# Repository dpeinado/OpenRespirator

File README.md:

# OpenRespirator
Software & Hardware for Open Respirator Project <br>

HW and system dodumentation are in the Doc directory <br>

## Contributors
- The system design is done by: Frede Jensen <br>
- Project coordination: Enrique Ramirez and Ramon Ruiz (Ennomotive) <br>
- Hardware & Software: David Ortiz, Rubén Perez de Aranda and Carlos Pardo <br>
- Collaborators: 
- - Intersurgical: Sara Rodriguez, Bill Barners, Mike Hinton <br>
- - Vithas Sanidad : Ignacio Narvaez <br>
- - McFly: Enrique, Marino y Daniel
  
## Sponsors: <br>

## ToDo list
### System

### Assembly

### Production
- Prepare production documentation
- - Define part alternatives
- Define production test & calibration
### Electronics
- Documentation
- - Electronics production test
### Firmware
- Monitor:
- Controller:
### Test & Validation
- Clinic test:
### Certification
- Documentation
- Presented to gobernment

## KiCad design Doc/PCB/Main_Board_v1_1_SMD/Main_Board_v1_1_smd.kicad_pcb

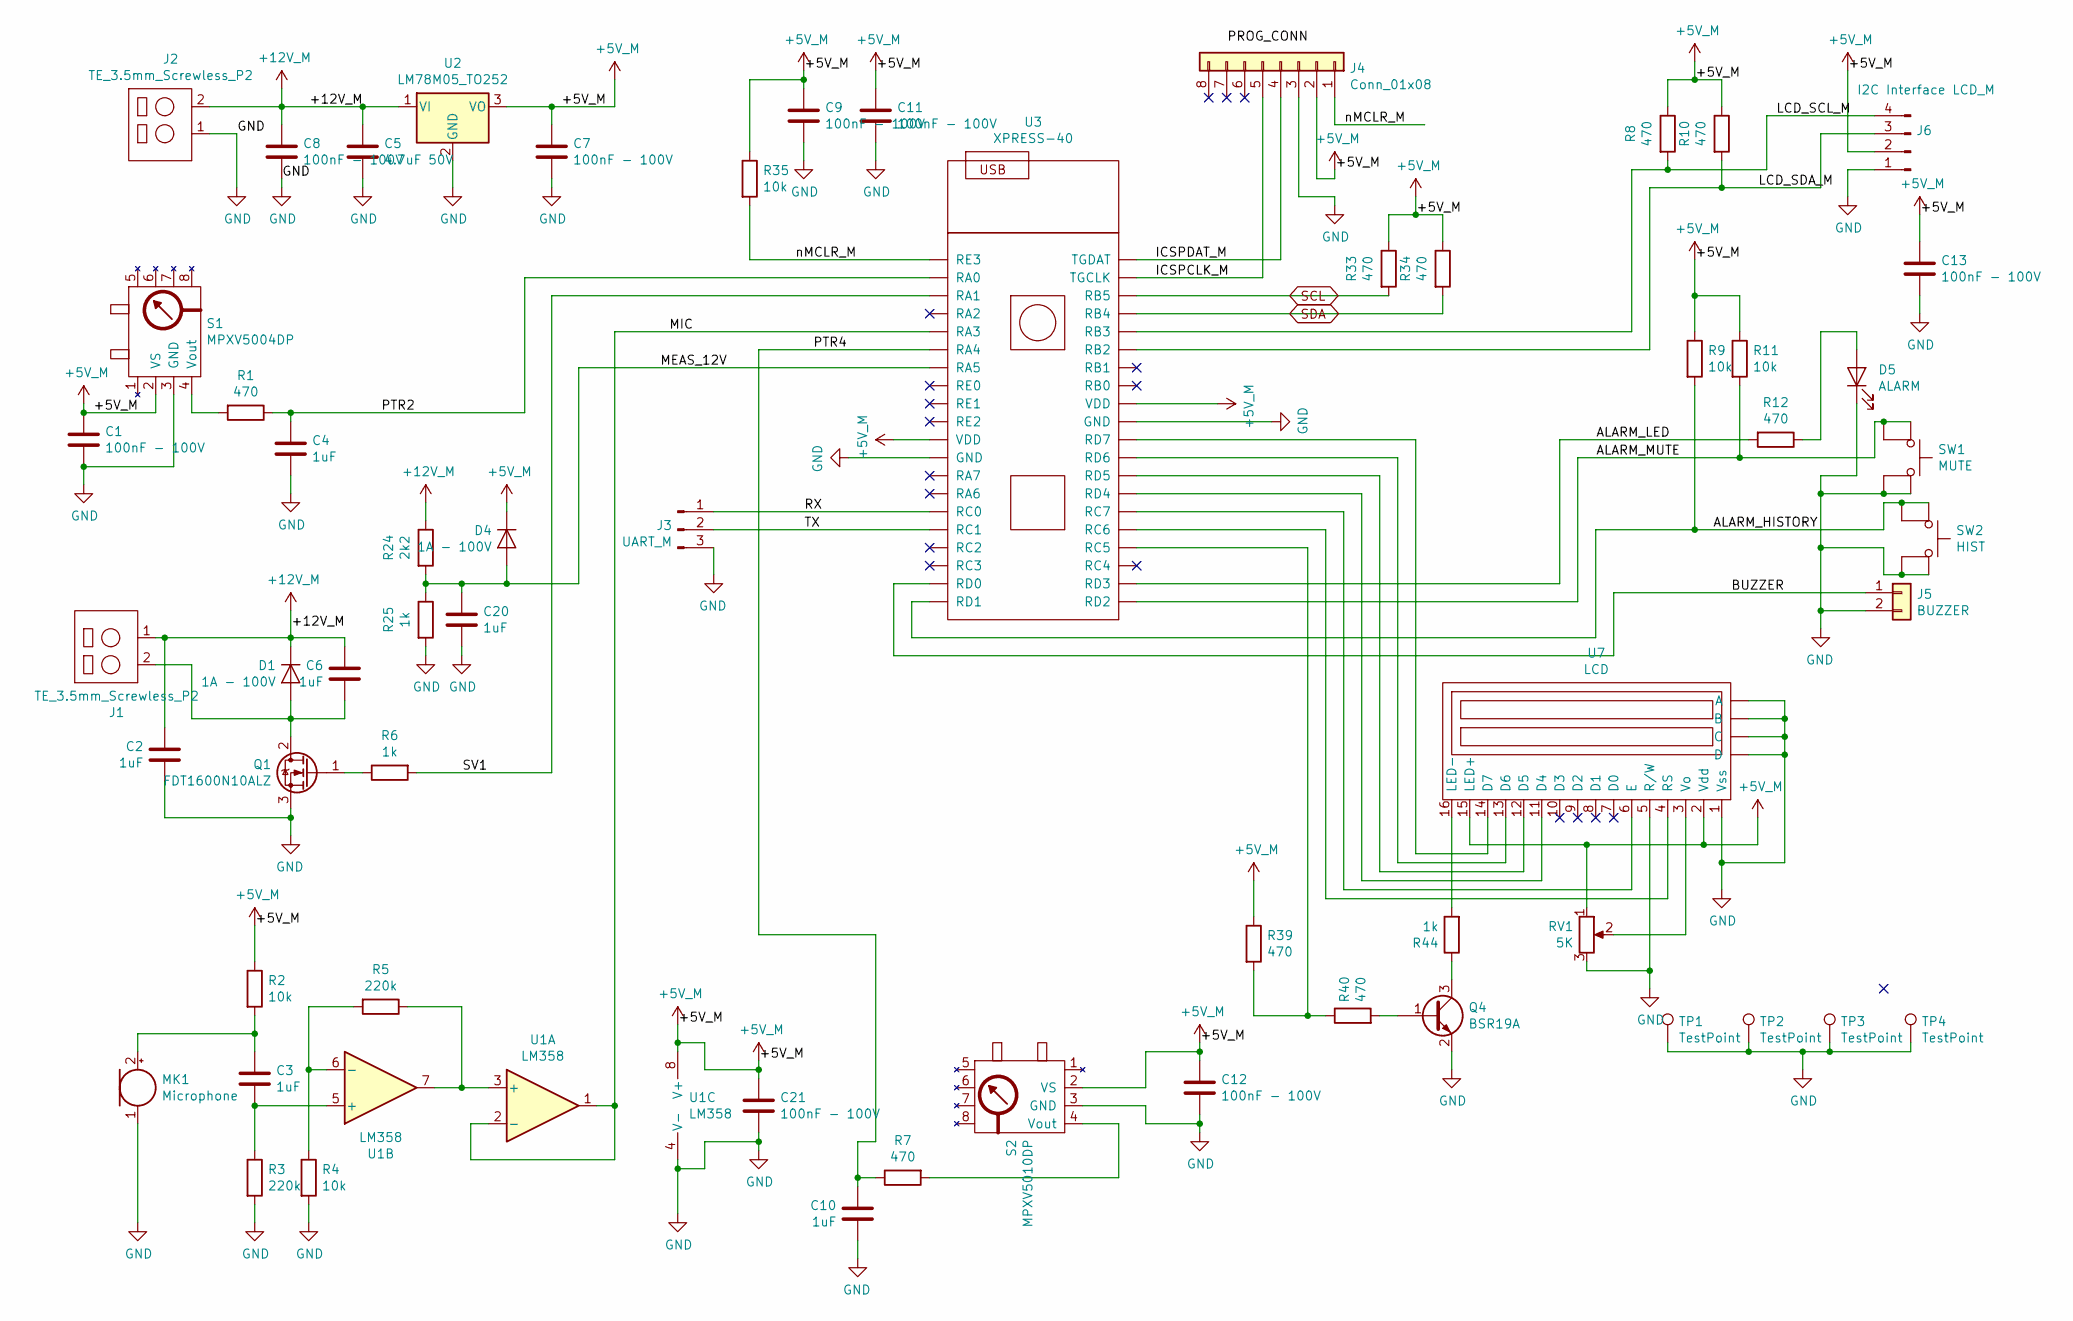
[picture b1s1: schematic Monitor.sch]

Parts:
C1, C7, C8, C9, C11, C12, C13, C21: 100nF - 100V; C_1206_3216Metric_Pad1.42x1.75mm_HandSolder
C2, C3, C4, C6, C10, C20: 1uF; C_1206_3216Metric_Pad1.42x1.75mm_HandSolder
C5: 4.7uF 50V; CP_Radial_D5.0mm_P2.00mm
D1, D4: 1A - 100V; D_SMA-SMB_Universal_Handsoldering
D5: ALARM; LED_D3.0mm
J1, J2: TE_3.5mm_Screwless_P2; PinHeader_1x02_Screwless_3.5mm
J3: UART_M; PinHeader_1x03_P2.54mm_Vertical
J4: Conn_01x08; PinHeader_1x08_P2.54mm_Horizontal
J5: BUZZER; PH_2_pol
J6: I2C Interface LCD_M; PH_4_pol
MK1: Microphone; MIC
Q1: FDT1600N10ALZ; SOT-223-3_TabPin2
Q4: BSR19A; TSOT-23
R1, R7, R8, R10, R12, R33, R34, R39, R40: 470; R_0603_1608Metric_Pad1.05x0.95mm_HandSolder
R2, R4, R9, R11, R35: 10k; R_0603_1608Metric_Pad1.05x0.95mm_HandSolder
R3, R5: 220k; R_0603_1608Metric_Pad1.05x0.95mm_HandSolder
R6, R25, R44: 1k; R_0603_1608Metric_Pad1.05x0.95mm_HandSolder
R24: 2k2; R_0603_1608Metric_Pad1.05x0.95mm_HandSolder
RV1: 5K; Potentiometer_Vishay_TS53YJ_Vertical
S1: MPXV5004DP; 1351-01
S2: MPXV5010DP; 1351-01
SW1: MUTE; SW_PUSH_6mm_H13mm
SW2: HIST; SW_PUSH_6mm_H13mm
TP1, TP2, TP3, TP4: TestPoint; LCD_DRILL
U1: LM358; SOIC-8-1EP_3.9x4.9mm_P1.27mm_EP2.41x3.3mm
U2: LM78M05_TO252; TO-252-2
U3: XPRESS-40; UQFN-40-1EP_5x5mm_P0.4mm_EP3.8x3.8mm
U7: LCD; LCD_2x16

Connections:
+5V_M: C1.1, C7.1, C9.1, C11.1, C12.1, C13.1, C21.1, D4.1 (K), J4.2, J6.2, R2.1, R8.1, R9.1, R10.1, R11.1, R33.1, R34.1, R35.1, R39.1, RV1.1, S1.2 (VS), S2.2 (VS), U1.8 (V+), U2.3 (VO), U3.11 (VDD), U3.32 (VDD), U7.2 (Vdd), U7.15 (LED+)
+12V_M: C2.1, C5.1, C6.1, C8.1, D1.1 (K), J1.1, J2.2, R24.1, U2.1 (VI)
/Monitor/ALARM_HISTORY: R9.2, SW2.1, U3.20 (RD1)
/Monitor/ALARM_LED: R12.2, U3.22 (RD3)
/Monitor/ALARM_MUTE: R11.2, SW1.1, U3.21 (RD2)
/Monitor/BUZZER: J5.1, U3.19 (RD0)
/Monitor/ICSPCLK_M: J4.5, U3.39 (TGCLK)
/Monitor/ICSPDAT_M: J4.4, U3.40 (TGDAT)
/Monitor/LCD_SCL_M: J6.4, R8.2, U3.36 (RB3)
/Monitor/LCD_SDA_M: J6.3, R10.2, U3.35 (RB2)
/Monitor/MEAS_12V: C20.1, D4.2 (A), R24.2, R25.1, U3.7 (RA5)
/Monitor/MIC: U1.1, U1.2 (-), U3.5 (RA3)
/Monitor/PTR2: C4.1, R1.1, U3.2 (RA0)
/Monitor/PTR4: C10.1, R7.1, U3.6 (RA4)
/Monitor/RX: J3.1, U3.15 (RC0)
/Monitor/SV1: R6.2, U3.3 (RA1)
/Monitor/TX: J3.2, U3.16 (RC1)
/Monitor/nMCLR_M: J4.1, R35.2, U3.1 (RE3)
GND: C1.2, C2.2, C4.2, C5.2, C7.2, C8.2, C9.2, C10.2, C11.2, C12.2, C13.2, C20.2, C21.2, D5.1 (K), J2.1, J3.3, J4.3, J5.2, J6.1, MK1.1 (-), Q1.3 (S), Q4.2 (E), R3.2, R4.2, R25.2, RV1.3, S1.3 (GND), S2.3 (GND), SW1.2, SW2.2, TP1.1, TP2.1, TP3.1, TP4.1, U1.4 (V-), U2.2 (GND), U3.12 (GND), U3.31 (GND), U7.1 (Vss), U7.5 (R/W), U7.~ (A); also elsewhere on the board
unnamed: C3.1, MK1.2 (+), R2.2
unnamed: C3.2, R3.1, U1.5 (+)
unnamed: C6.2, D1.2 (A), J1.2, Q1.2 (D)
unnamed: D5.2 (A), R12.1
unnamed: Q1.1 (G), R6.1
unnamed: Q4.1 (B), R40.2
unnamed: Q4.3 (C), R44.1
unnamed: R1.2, S1.4 (Vout)
unnamed: R4.1, R5.2, U1.6 (-)
unnamed: R5.1, U1.3 (+), U1.7
unnamed: R7.2, S2.4 (Vout)
unnamed: R39.2, R40.1, U3.24 (RC5)
unnamed: R44.2, U7.16 (LED-)
unnamed: RV1.2, U7.3 (Vo)
unnamed: U3.25 (RC6), U7.4 (RS)
unnamed: U3.26 (RC7), U7.6 (E)
unnamed: U3.27 (RD4), U7.11 (D4)
unnamed: U3.28 (RD5), U7.12 (D5)
unnamed: U3.29 (RD6), U7.13 (D6)
unnamed: U3.30 (RD7), U7.14 (D7)
SCL: R33.2, U3.38 (RB5); also elsewhere on the board
SDA: R34.2, U3.37 (RB4); also elsewhere on the board

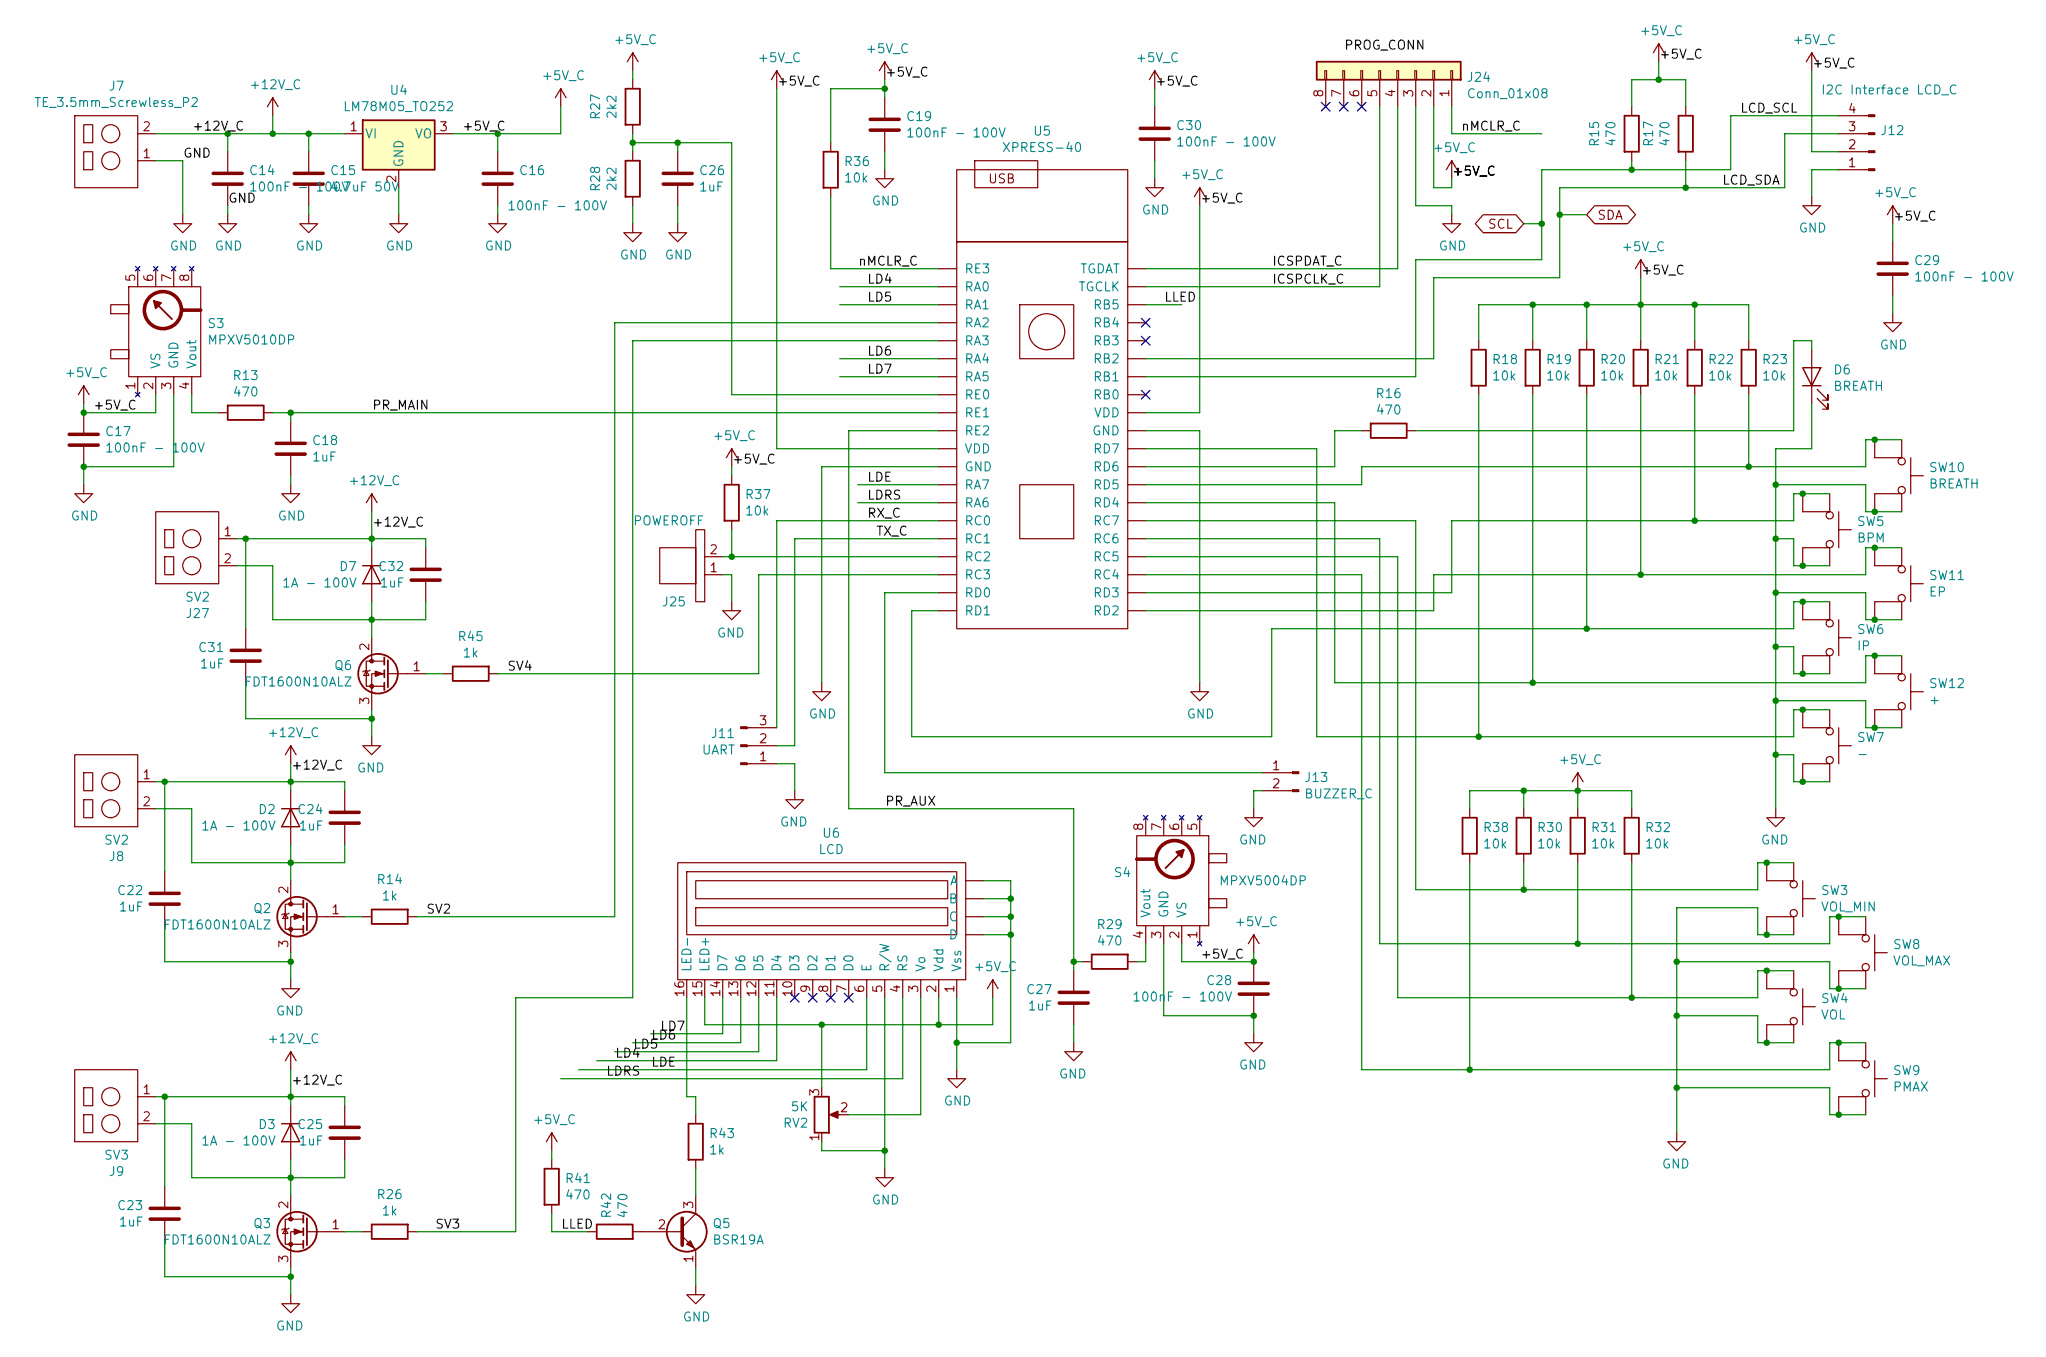
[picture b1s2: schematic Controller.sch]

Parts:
C14, C16, C17, C19, C28, C29, C30: 100nF - 100V; C_1206_3216Metric_Pad1.42x1.75mm_HandSolder
C15: 4.7uF 50V; CP_Radial_D5.0mm_P2.00mm
C18, C22, C23, C24, C25, C26, C27, C31, C32: 1uF; C_1206_3216Metric_Pad1.42x1.75mm_HandSolder
D2, D3, D7: 1A - 100V; D_SMA-SMB_Universal_Handsoldering
D6: BREATH; LED_D3.0mm
J7: TE_3.5mm_Screwless_P2; PinHeader_1x02_Screwless_3.5mm
J8, J27: SV2; PinHeader_1x02_Screwless_3.5mm
J9: SV3; PinHeader_1x02_Screwless_3.5mm
J11: UART; PinHeader_1x03_P2.54mm_Vertical
J12: I2C Interface LCD_C; PH_4_pol
J13: BUZZER_C; PinHeader_1x02_P2.54mm_Vertical
J24: Conn_01x08; PinHeader_1x08_P2.54mm_Horizontal
J25: POWEROFF; PH_2_pol
Q2, Q3, Q6: FDT1600N10ALZ; SOT-223-3_TabPin2
Q5: BSR19A; TSOT-23
R13, R15, R16, R17, R29, R41, R42: 470; R_0603_1608Metric_Pad1.05x0.95mm_HandSolder
R14, R26, R43, R45: 1k; R_0603_1608Metric_Pad1.05x0.95mm_HandSolder
R18, R19, R20, R21, R22, R23, R30, R31, R32, R36, R37, R38: 10k; R_0603_1608Metric_Pad1.05x0.95mm_HandSolder
R27, R28: 2k2; R_0603_1608Metric_Pad1.05x0.95mm_HandSolder
RV2: 5K; Potentiometer_Vishay_TS53YJ_Vertical
S3: MPXV5010DP; 1351-01
S4: MPXV5004DP; 1351-01
SW3: VOL_MIN; SW_PUSH_6mm_H13mm
SW4: VOL; SW_PUSH_6mm_H13mm
SW5: BPM; SW_PUSH_6mm_H13mm
SW6: IP; SW_PUSH_6mm_H13mm
SW7: -; SW_PUSH_6mm_H13mm
SW8: VOL_MAX; SW_PUSH_6mm_H13mm
SW9: PMAX; SW_PUSH_6mm_H13mm
SW10: BREATH; SW_PUSH_6mm_H13mm
SW11: EP; SW_PUSH_6mm_H13mm
SW12: +; SW_PUSH_6mm_H13mm
U4: LM78M05_TO252; TO-252-2
U5: XPRESS-40; UQFN-40-1EP_5x5mm_P0.4mm_EP3.8x3.8mm
U6: LCD; LCD_2x16

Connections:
+5V_C: C16.1, C17.1, C19.1, C28.1, C29.1, C30.1, J12.2, J24.2, R15.1, R17.1, R18.1, R19.1, R20.1, R21.1, R22.1, R23.1, R27.1, R30.1, R31.1, R32.1, R36.1, R37.1, R38.1, R41.1, RV2.3, S3.2 (VS), S4.2 (VS), U4.3 (VO), U5.11 (VDD), U5.32 (VDD), U6.2 (Vdd), U6.15 (LED+)
+12V_C: C14.1, C15.1, C22.1, C23.1, C24.1, C25.1, C31.1, C32.1, D2.1 (K), D3.1 (K), D7.1 (K), J7.2, J8.1, J9.1, J27.1, U4.1 (VI)
/Controller/ICSPCLK_C: J24.5, U5.39 (TGCLK)
/Controller/ICSPDAT_C: J24.4, U5.40 (TGDAT)
/Controller/LD4: U5.2 (RA0), U6.11 (D4)
/Controller/LD5: U5.3 (RA1), U6.12 (D5)
/Controller/LD6: U5.6 (RA4), U6.13 (D6)
/Controller/LD7: U5.7 (RA5), U6.14 (D7)
/Controller/LDE: U5.13 (RA7), U6.6 (E)
/Controller/LDRS: U5.14 (RA6), U6.4 (RS)
/Controller/LLED: R41.2, R42.1, U5.38 (RB5)
/Controller/PR_AUX: C27.1, R29.1, U5.10 (RE2)
/Controller/PR_MAIN: C18.1, R13.1, U5.9 (RE1)
/Controller/RX_C: J11.3, U5.15 (RC0)
/Controller/SV2: R14.2, U5.4 (RA2)
/Controller/SV3: R26.2, U5.5 (RA3)
/Controller/SV4: R45.2, U5.18 (RC3)
/Controller/TX_C: J11.2, U5.16 (RC1)
/Controller/nMCLR_C: J24.1, R36.2, U5.1 (RE3)
GND: C14.2, C15.2, C16.2, C17.2, C18.2, C19.2, C22.2, C23.2, C26.2, C27.2, C28.2, C29.2, C30.2, C31.2, D6.1 (K), J7.1, J11.1, J12.1, J13.2, J24.3, J25.1, Q2.3 (S), Q3.3 (S), Q5.1 (E), Q6.3 (S), R28.2, RV2.1, S3.3 (GND), S4.3 (GND), SW3.2, SW4.2, SW5.2, SW6.2, SW7.2, SW8.2, SW9.2, SW10.2, SW11.2, SW12.2, U4.2 (GND), U5.12 (GND), U5.31 (GND), U6.1 (Vss), U6.5 (R/W), U6.~ (A); also elsewhere on the board
unnamed: C24.2, D2.2 (A), J8.2, Q2.2 (D)
unnamed: C25.2, D3.2 (A), J9.2, Q3.2 (D)
unnamed: C26.1, R27.2, R28.1, U5.8 (RE0)
unnamed: C32.2, D7.2 (A), J27.2, Q6.2 (D)
unnamed: D6.2 (A), R16.1
unnamed: J13.1, U5.19 (RD0)
unnamed: J25.2, R37.2, U5.17 (RC2)
unnamed: Q2.1 (G), R14.1
unnamed: Q3.1 (G), R26.1
unnamed: Q5.2 (B), R42.2
unnamed: Q5.3 (C), R43.2
unnamed: Q6.1 (G), R45.1
unnamed: R13.2, S3.4 (Vout)
unnamed: R16.2, U5.29 (RD6)
unnamed: R18.2, SW7.1, U5.30 (RD7)
unnamed: R19.2, SW12.1, U5.27 (RD4)
unnamed: R20.2, SW6.1, U5.20 (RD1)
unnamed: R21.2, SW11.1, U5.21 (RD2)
unnamed: R22.2, SW5.1, U5.22 (RD3)
unnamed: R23.2, SW10.1, U5.28 (RD5)
unnamed: R29.2, S4.4 (Vout)
unnamed: R30.2, SW3.1, U5.26 (RC7)
unnamed: R31.2, SW8.1, U5.25 (RC6)
unnamed: R32.2, SW4.1, U5.24 (RC5)
unnamed: R38.2, SW9.1, U5.23 (RC4)
unnamed: R43.1, U6.16 (LED-)
unnamed: RV2.2, U6.3 (Vo)
SCL: J12.4, R15.2, U5.34 (RB1); also elsewhere on the board
SDA: J12.3, R17.2, U5.35 (RB2); also elsewhere on the board

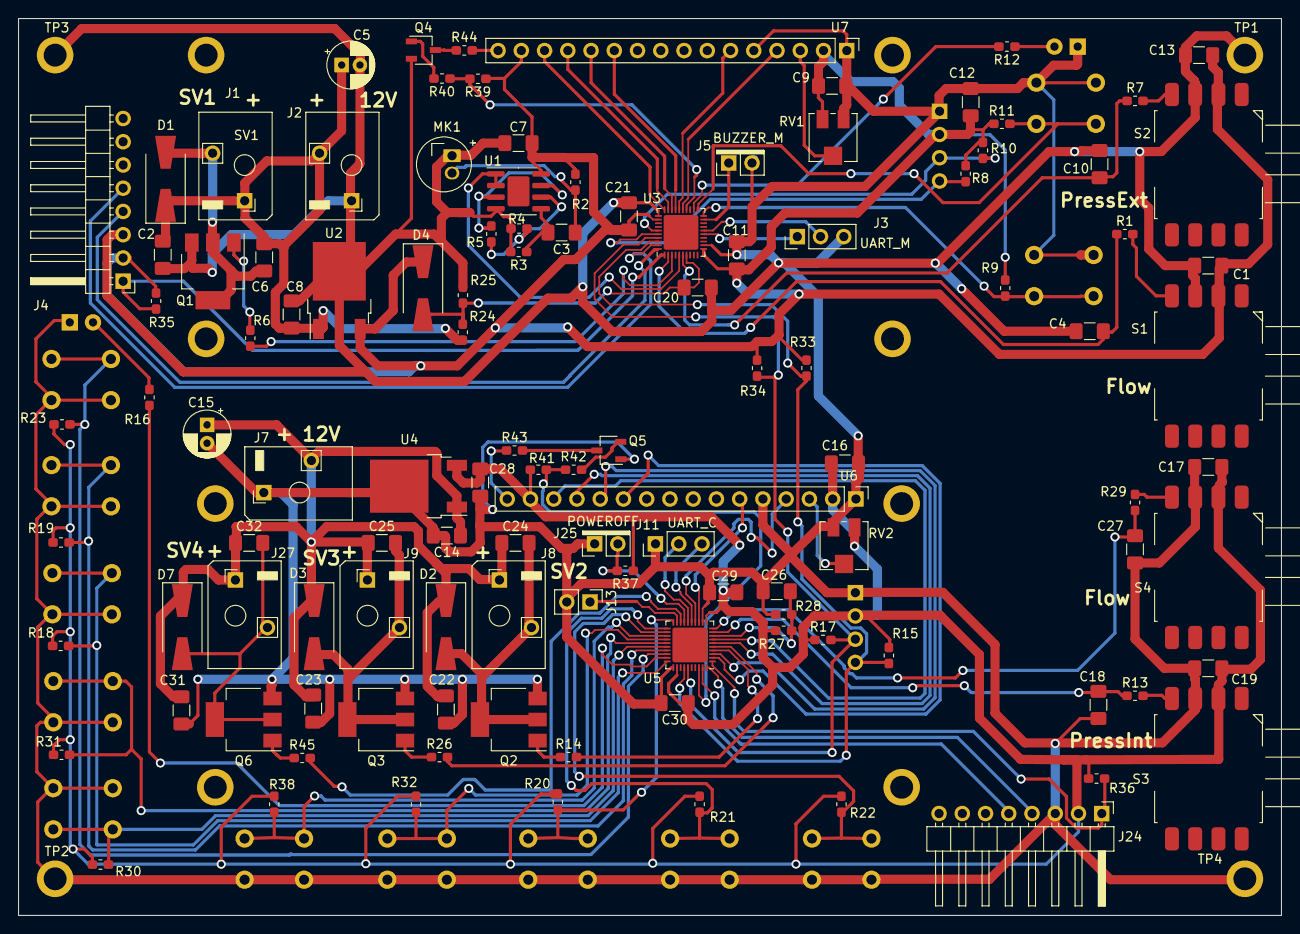
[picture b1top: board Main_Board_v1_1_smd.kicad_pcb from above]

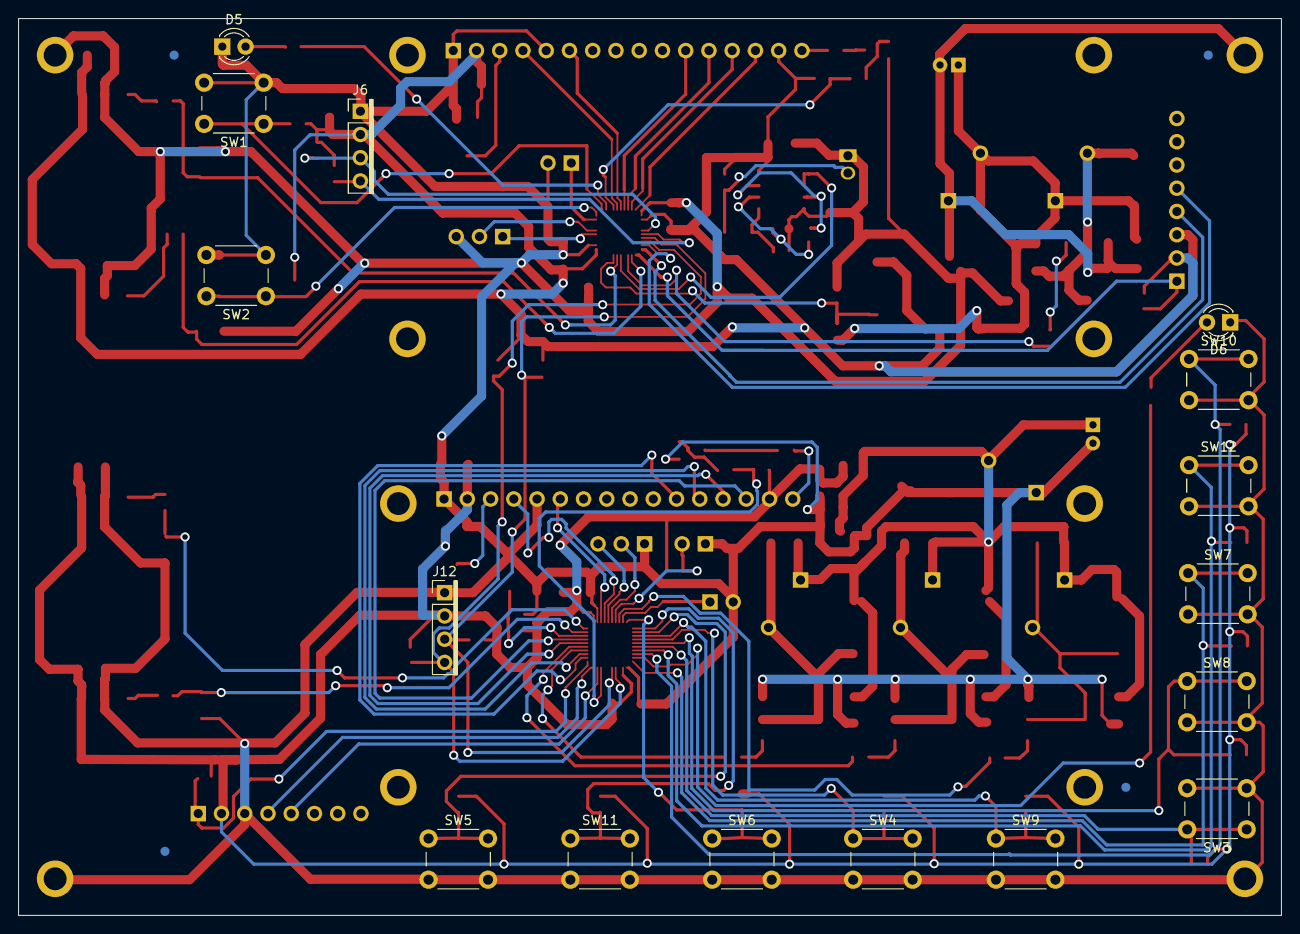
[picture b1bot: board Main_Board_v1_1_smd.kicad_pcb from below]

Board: 2 copper layers, 138.0 x 98.0 mm, 139 parts (16 on the bottom side), 87 nets.

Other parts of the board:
FIDUCIAL_TEST_PCB_1C, FIDUCIAL_TEST_PCB_1C#2, FIDUCIAL_TEST_PCB_1C#3, FIDUCIAL_TEST_PCB_1C#4: VAL**; FIDUCIAL_TEST_PCB_1C

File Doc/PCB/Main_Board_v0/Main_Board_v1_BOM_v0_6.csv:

Reference, Quantity, Value, Footprint, Datasheet
C10 C2 C6 C3 C4 C20 C22 C24 C23 C25 C18 C27 C26 ,13,"1uF","Capacitor_THT:C_Rect_L13.0mm_W4.0mm_P10.00mm_FKS3_FKP3_MKS4","https://es.rs-online.com/web/p/condensadores-de-pelicula-de-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"
C12 C13 C11 C8 C9 C1 C7 C21 C19 C14 C16 C29 C17 C28 C30 ,15,"100nF - 100V","Capacitor_THT:C_Rect_L7.2mm_W2.5mm_P5.00mm_FKS2_FKP2_MKS2_MKP2","https://es.rs-online.com/web/p/condensadores-de-pelicula-de-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"
C5 C15 ,2,"4.7uF 50V","Capacitor_THT:CP_Radial_D5.0mm_P2.00mm","https://es.rs-online.com/web/p/condensadores-de-aluminio/1701286/"
D1 D4 D2 D3 ,4,"1N4007","Diode_THT:D_DO-41_SOD81_P10.16mm_Horizontal","https://es.rs-online.com/web/p/diodos-schottky-y-rectificado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"
J10 ,1,"BPM","Ventilator:PushButton","https://es.rs-online.com/web/p/botones-pulsadores/7346827/"
J11 ,1,"UART","Connector_PinHeader_2.54mm:PinHeader_1x03_P2.54mm_Vertical","~"
J12 ,1,"I2C Interface LCD_C","Ventilator:PH_4_pol","~"
J13 ,1,"BUZZER_C","Connector_PinHeader_2.54mm:PinHeader_1x02_P2.54mm_Vertical","https://es.rs-online.com/web/p/componentes-de-piezo-buzzer/6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"
J14 ,1,"MUTE","Ventilator:PushButton_LED","https://es.rs-online.com/web/p/botones-pulsadores/8207521/"
J15 ,1,"HISTORY","Ventilator:PushButton","https://es.rs-online.com/web/p/botones-pulsadores/7346827/"
J16 ,1,"IP","Ventilator:PushButton","https://es.rs-online.com/web/p/botones-pulsadores/7346827/"
J17 ,1,"-","Ventilator:PushButton","https://es.rs-online.com/web/p/botones-pulsadores/7346827/"
J18 ,1,"BREATH","Ventilator:PushButton_LED","https://es.rs-online.com/web/p/botones-pulsadores/8207533/"
J19 ,1,"EP","Ventilator:PushButton","https://es.rs-online.com/web/p/botones-pulsadores/7346827/"
J2 J1 J7 ,3,"TE_3.5mm_Screwless_P2","Ventilator:PinHeader_1x02_Screwless_3.5mm","https://es.rs-online.com/web/p/bloques-terminales-para-pcb/1232052/"
J20 ,1,"+","Ventilator:PushButton","https://es.rs-online.com/web/p/botones-pulsadores/7346827/"
J21 ,1,"VOL_MIN","Ventilator:PushButton","https://es.rs-online.com/web/p/botones-pulsadores/7346827/"
J22 ,1,"VOL","Ventilator:PushButton","https://es.rs-online.com/web/p/botones-pulsadores/7346827/"
J23 ,1,"VOL_MAX","Ventilator:PushButton","https://es.rs-online.com/web/p/botones-pulsadores/7346827/"
J3 ,1,"UART_M","Connector_PinHeader_2.54mm:PinHeader_1x03_P2.54mm_Vertical","~"
J4 J24 ,2,"Conn_01x08","Connector_PinHeader_2.54mm:PinHeader_1x08_P2.54mm_Horizontal","~"
J5 ,1,"BUZZER","Ventilator:PH_2_pol","https://es.rs-online.com/web/p/componentes-de-piezo-buzzer/6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"
J6 ,1,"I2C Interface LCD_M","Ventilator:PH_4_pol","~"
J8 ,1,"SV2","Ventilator:PinHeader_1x02_Screwless_3.5mm","https://es.rs-online.com/web/p/bloques-terminales-para-pcb/1232052/"
J9 ,1,"SV3","Ventilator:PinHeader_1x02_Screwless_3.5mm","https://es.rs-online.com/web/p/bloques-terminales-para-pcb/1232052/"
MK1 ,1,"Microphone","Ventilator:MIC","https://es.rs-online.com/web/p/componentes-de-microfono-para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"
Q1 Q2 Q3 ,3,"STP24NF10 ","Package_TO_SOT_THT:TO-220-3_Vertical","https://es.rs-online.com/web/p/mosfet/6875377/"
R24 ,1,"22k","Resistor_THT:R_Axial_DIN0207_L6.3mm_D2.5mm_P10.16mm_Horizontal","~"
R3 R5 ,2,"220k","Resistor_THT:R_Axial_DIN0207_L6.3mm_D2.5mm_P10.16mm_Horizontal","~"
R4 R2 R11 R9 R25 R35 R19 R20 R21 R22 R23 R18 R27 R28 R31 R32 R30 R36 ,18,"10k","Resistor_THT:R_Axial_DIN0207_L6.3mm_D2.5mm_P10.16mm_Horizontal","~"
R6 R14 R26 ,3,"50","Resistor_THT:R_Axial_DIN0207_L6.3mm_D2.5mm_P10.16mm_Horizontal","~"
R7 R10 R8 R12 R1 R34 R33 R16 R17 R15 R13 R29 ,12,"470","Resistor_THT:R_Axial_DIN0207_L6.3mm_D2.5mm_P10.16mm_Horizontal","~"
S1 S2 S3 S4 ,4,"MPXV5004DP","Ventilator:1351-01","https://es.rs-online.com/web/p/sensores-de-presion/9227399/"
TP3 TP2 TP1 TP4 TP7 TP6 TP5 TP8 TP12 TP11 TP10 TP13 ,12,"TestPoint","Ventilator:LCD_DRILL","~"
TP9 ,1,"TestPoint_Alt","Ventilator:pcb","~"
U1 ,1,"LM358","Package_DIP:DIP-8_W7.62mm_LongPads","http://www.ti.com/lit/ds/symlink/lm2904-n.pdf"
U2 U4 ,2,"LM7805_TO220","Package_TO_SOT_THT:TO-220-3_Vertical","http://www.fairchildsemi.com/ds/LM/LM7805.pdf"
U3 U5 ,2,"XPRESS-40","Ventilator:EXPRESS-40_DIP_40","https://es.rs-online.com/web/p/kits-de-desarrollo-de-procesa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"

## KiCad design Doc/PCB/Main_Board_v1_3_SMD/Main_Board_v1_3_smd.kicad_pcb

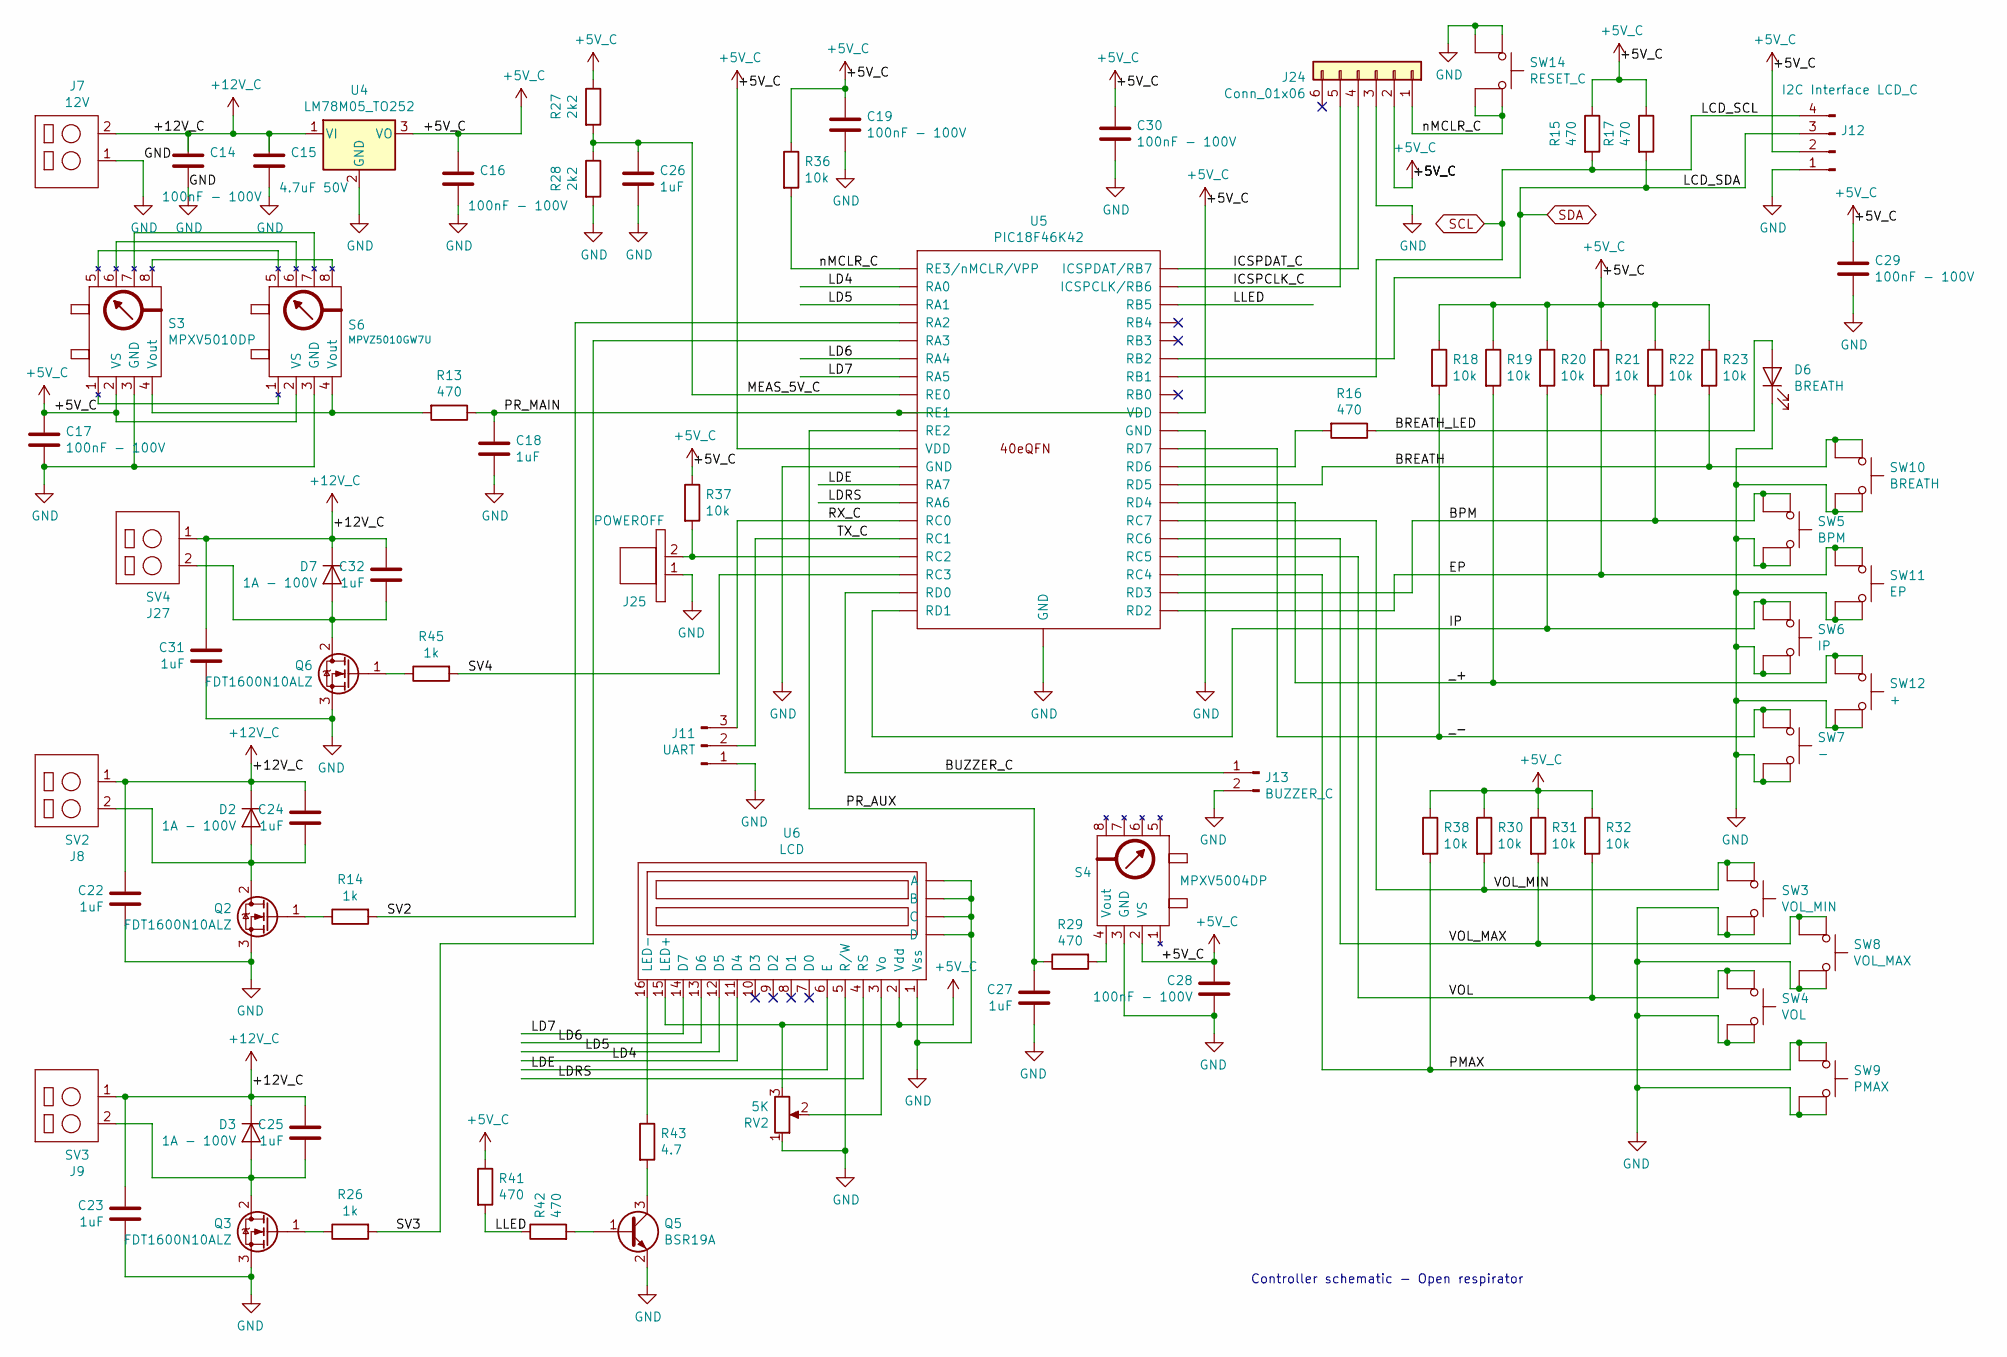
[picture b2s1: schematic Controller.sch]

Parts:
C14, C16, C17, C19, C28, C29, C30: 100nF - 100V; C_1206_3216Metric_Pad1.42x1.75mm_HandSolder
C15: 4.7uF 50V; CP_Radial_D5.0mm_P2.00mm
C18, C22, C23, C24, C25, C26, C27, C31, C32: 1uF; C_1206_3216Metric_Pad1.42x1.75mm_HandSolder
D2, D3, D7: 1A - 100V; D_SMA-SMB_Universal_Handsoldering
D6: BREATH; LED_D3.0mm
J7: 12V; PinHeader_1x02_Screwless_3.5mm
J8: SV2; PinHeader_1x02_Screwless_3.5mm
J9: SV3; PinHeader_1x02_Screwless_3.5mm
J11: UART; PinHeader_1x03_P2.54mm_Vertical
J12: I2C Interface LCD_C; PH_4_pol
J13: BUZZER_C; PinHeader_1x02_P2.54mm_Vertical
J24: Conn_01x06; PinHeader_1x06_P2.54mm_Horizontal
J25: POWEROFF; PH_2_pol
J27: SV4; PinHeader_1x02_Screwless_3.5mm
Q2, Q3, Q6: FDT1600N10ALZ; SOT-223-3_TabPin2
Q5: BSR19A; SOT-23
R13, R15, R16, R17, R29, R41, R42: 470; R_0603_1608Metric_Pad1.05x0.95mm_HandSolder
R14, R26, R45: 1k; R_0603_1608Metric_Pad1.05x0.95mm_HandSolder
R18, R19, R20, R21, R22, R23, R30, R31, R32, R36, R37, R38: 10k; R_0603_1608Metric_Pad1.05x0.95mm_HandSolder
R27, R28: 2k2; R_0603_1608Metric_Pad1.05x0.95mm_HandSolder
R43: 4.7; R_0603_1608Metric_Pad1.05x0.95mm_HandSolder
RV2: 5K; Potentiometer_Vishay_TS53YJ_Vertical
S3: MPXV5010DP; 1351-01
S4: MPXV5004DP; 1351-01
S6: MPVZ5010GW7U; 1560-03
SW3: VOL_MIN; SW_PUSH_6mm_H13mm
SW4: VOL; SW_PUSH_6mm_H13mm
SW5: BPM; SW_PUSH_6mm_H13mm
SW6: IP; SW_PUSH_6mm_H13mm
SW7: -; SW_PUSH_6mm_H13mm
SW8: VOL_MAX; SW_PUSH_6mm_H13mm
SW9: PMAX; SW_PUSH_6mm_H13mm
SW10: BREATH; SW_PUSH_6mm_H13mm
SW11: EP; SW_PUSH_6mm_H13mm
SW12: +; SW_PUSH_6mm_H13mm
SW14: RESET_C; SW_PUSH_6mm_H13mm
U4: LM78M05_TO252; TO-252-2
U5: PIC18F46K42; QFN-40-1EP_5x5mm_P0.4mm_EP3.6x3.6mm_MedThermalVias
U6: LCD; LCD_2x16

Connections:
+5V_C: C16.1, C17.1, C19.1, C28.1, C29.1, C30.1, J12.2, J24.2, R15.1, R17.1, R18.1, R19.1, R20.1, R21.1, R22.1, R23.1, R27.1, R30.1, R31.1, R32.1, R36.1, R37.1, R38.1, R41.1, RV2.3, S3.2 (VS), S4.2 (VS), S6.2 (VS), U4.3 (VO), U5.7 (VDD), U5.26 (VDD), U6.2 (Vdd), U6.15 (LED+)
+12V_C: C14.1, C15.1, C22.1, C23.1, C24.1, C25.1, C31.1, C32.1, D2.1 (K), D3.1 (K), D7.1 (K), J7.2, J8.1, J9.1, J27.1, U4.1 (VI)
/Controller/BPM: R22.2, SW5.1, U5.37 (RD3)
/Controller/BREATH: R23.2, SW10.1, U5.3 (RD5)
/Controller/BREATH_LED: D6.2 (A), R16.1
/Controller/BUZZER_C: J13.1, U5.34 (RD0)
/Controller/EP: R21.2, SW11.1, U5.36 (RD2)
/Controller/ICSPCLK_C: J24.5, U5.14 (ICSPCLK/RB6)
/Controller/ICSPDAT_C: J24.4, U5.15 (ICSPDAT/RB7)
/Controller/IP: R20.2, SW6.1, U5.35 (RD1)
/Controller/LD4: U5.17 (RA0), U6.11 (D4)
/Controller/LD5: U5.18 (RA1), U6.12 (D5)
/Controller/LD6: U5.21 (RA4), U6.13 (D6)
/Controller/LD7: U5.22 (RA5), U6.14 (D7)
/Controller/LDE: U5.28 (RA7), U6.6 (E)
/Controller/LDRS: U5.29 (RA6), U6.4 (RS)
/Controller/LLED: R41.2, R42.1, U5.13 (RB5)
/Controller/MEAS_5V_C: C26.1, R27.2, R28.1, U5.23 (RE0)
/Controller/PMAX: R38.2, SW9.1, U5.38 (RC4)
/Controller/PR_AUX: C27.1, R29.1, U5.25 (RE2)
/Controller/PR_MAIN: C18.1, R13.1, U5.24 (RE1)
/Controller/RX_C: J11.3, U5.30 (RC0)
/Controller/SV2: R14.2, U5.19 (RA2)
/Controller/SV3: R26.2, U5.20 (RA3)
/Controller/SV4: R45.2, U5.33 (RC3)
/Controller/TX_C: J11.2, U5.31 (RC1)
/Controller/VOL: R32.2, SW4.1, U5.39 (RC5)
/Controller/VOL_MAX: R31.2, SW8.1, U5.40 (RC6)
/Controller/VOL_MIN: R30.2, SW3.1, U5.1 (RC7)
/Controller/_+: R19.2, SW12.1, U5.2 (RD4)
/Controller/_-: R18.2, SW7.1, U5.5 (RD7)
/Controller/nMCLR_C: J24.1, R36.2, SW14.2, U5.16 (RE3/nMCLR/VPP)
GND: C14.2, C15.2, C16.2, C17.2, C18.2, C19.2, C22.2, C23.2, C26.2, C27.2, C28.2, C29.2, C30.2, C31.2, D6.1 (K), J7.1, J11.1, J12.1, J13.2, J24.3, J25.1, Q2.3 (S), Q3.3 (S), Q5.2 (E), Q6.3 (S), R28.2, RV2.1, S3.3 (GND), S4.3 (GND), S6.3 (GND), SW3.2, SW4.2, SW5.2, SW6.2, SW7.2, SW8.2, SW9.2, SW10.2, SW11.2, SW12.2, SW14.1, U4.2 (GND), U5.6 (GND), U5.27 (GND), U5.41 (GND), U6.1 (Vss), U6.5 (R/W), U6.~ (A); also elsewhere on the board
unnamed: C24.2, D2.2 (A), J8.2, Q2.2 (D)
unnamed: C25.2, D3.2 (A), J9.2, Q3.2 (D)
unnamed: C32.2, D7.2 (A), J27.2, Q6.2 (D)
unnamed: J25.2, R37.2, U5.32 (RC2)
unnamed: Q2.1 (G), R14.1
unnamed: Q3.1 (G), R26.1
unnamed: Q5.1 (B), R42.2
unnamed: Q5.3 (C), R43.2
unnamed: Q6.1 (G), R45.1
unnamed: R13.2, S3.4 (Vout), S6.4 (Vout)
unnamed: R16.2, U5.4 (RD6)
unnamed: R29.2, S4.4 (Vout)
unnamed: R43.1, U6.16 (LED-)
unnamed: RV2.2, U6.3 (Vo)
unnamed: S3.1, S6.1
unnamed: S3.5, S6.5
unnamed: S3.6, S6.6
unnamed: S3.7, S6.7
unnamed: S3.8, S6.8
SCL: J12.4, R15.2, U5.9 (RB1); also elsewhere on the board
SDA: J12.3, R17.2, U5.10 (RB2); also elsewhere on the board

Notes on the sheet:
Controller schematic - Open respirator

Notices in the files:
Controller.X/mcc_generated_files/pin_manager.h:
(c) 2018 Microchip Technology Inc. and its subsidiaries.
Doc/PCB/Main_Board_v1_3_SMD/Main_Board_v1_3_smd.kicad_pcb:
GNU-GPL2
